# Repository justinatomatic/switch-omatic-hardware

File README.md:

## Switch-Omatic Board design

Eagle files for the Switch-Omatic project aka Wireless SmartHome Buttons. 

Current prototypes are using the 0.2 files
0.3 is work in progress for the next version. 

Parts from the Sparkfun and Adafruit libraries used.

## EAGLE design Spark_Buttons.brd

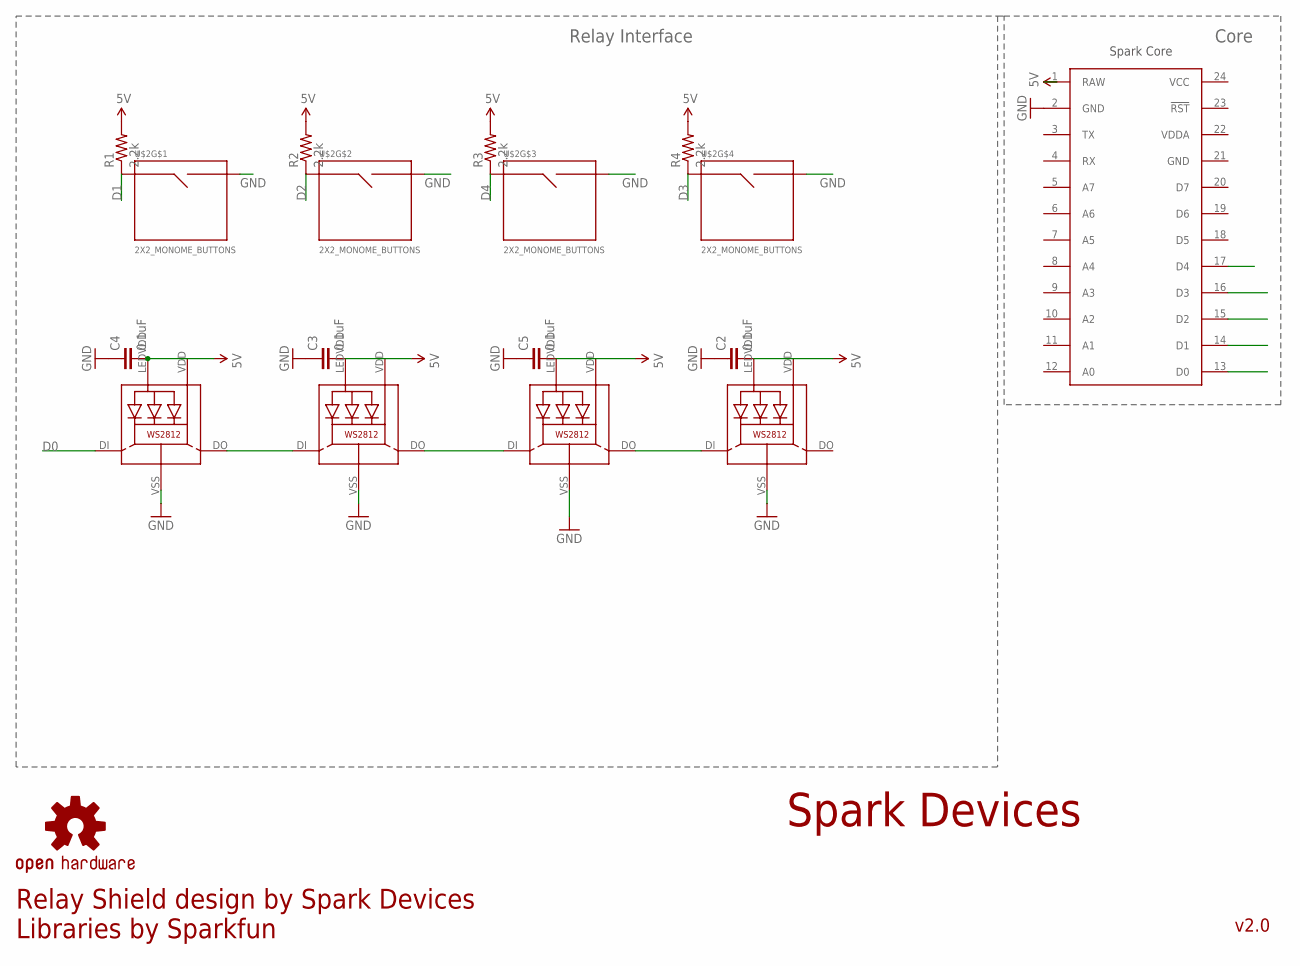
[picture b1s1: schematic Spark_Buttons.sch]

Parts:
C2, C3, C4, C5: 0.1uF; 0603-CAP
LED1, LED2, LED3, LED4: WS2812
LOGO1: OSHW-LOGOM; OSHW-LOGO-M
R1, R2, R3, R4: 2.2k; 0603-RES
U$1: SPARK_CORECORE; SPARK_CORE
U$2: 2X2_MONOME_BUTTONS; 2X2_MONOME_PAD

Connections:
5V: C2.2, C3.2, C4.2, C5.2, LED1.LEDVDD, LED1.VDD, LED2.LEDVDD, LED2.VDD, LED3.LEDVDD, LED3.VDD, LED4.LEDVDD, LED4.VDD, R1.2, R2.2, R3.2, R4.2, U$1.1 (RAW)
D0: LED1.DI, U$1.13 (D0)
D1: R1.1, U$1.14 (D1), U$2.SIG1
D2: R2.1, U$1.15 (D2), U$2.SIG3 (SIG1)
D3: R4.1, U$1.16 (D3), U$2.SIG7 (SIG1)
D4: R3.1, U$1.17 (D4), U$2.SIG5 (SIG1)
GND: C2.1, C3.1, C4.1, C5.1, LED1.VSS (GND), LED2.VSS (GND), LED3.VSS (GND), LED4.VSS (GND), U$1.2 (GND), U$1.21 (GND), U$2.SIG2, U$2.SIG4 (SIG2), U$2.SIG6 (SIG2), U$2.SIG8 (SIG2)
unnamed: LED1.DO, LED2.DI
unnamed: LED2.DO, LED3.DI
unnamed: LED3.DO, LED4.DI
VCC: U$1.24 (VCC)
VDDA: U$1.22 (VDDA)

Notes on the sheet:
Spark Core
Spark Devices
Core
Relay Interface
Relay Shield design by Spark Devices Libraries by Sparkfun
v2.0

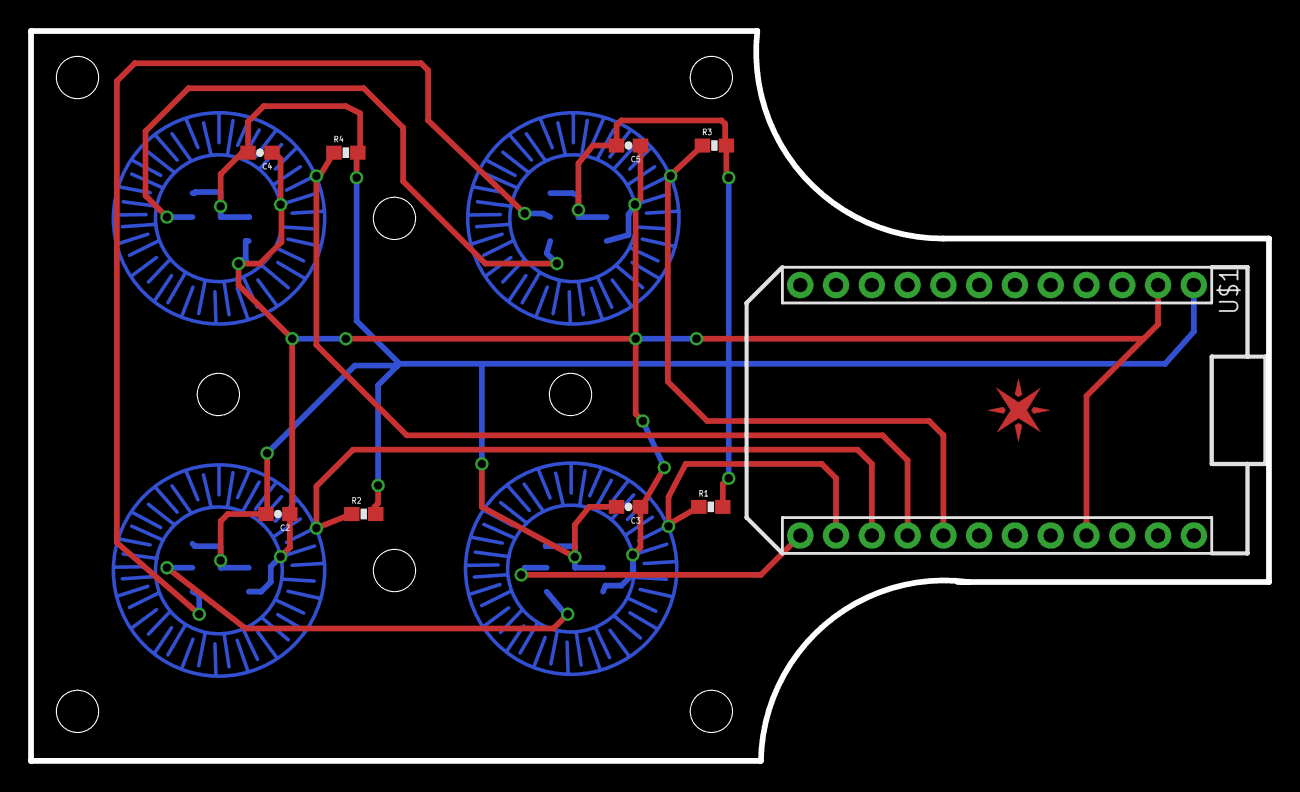
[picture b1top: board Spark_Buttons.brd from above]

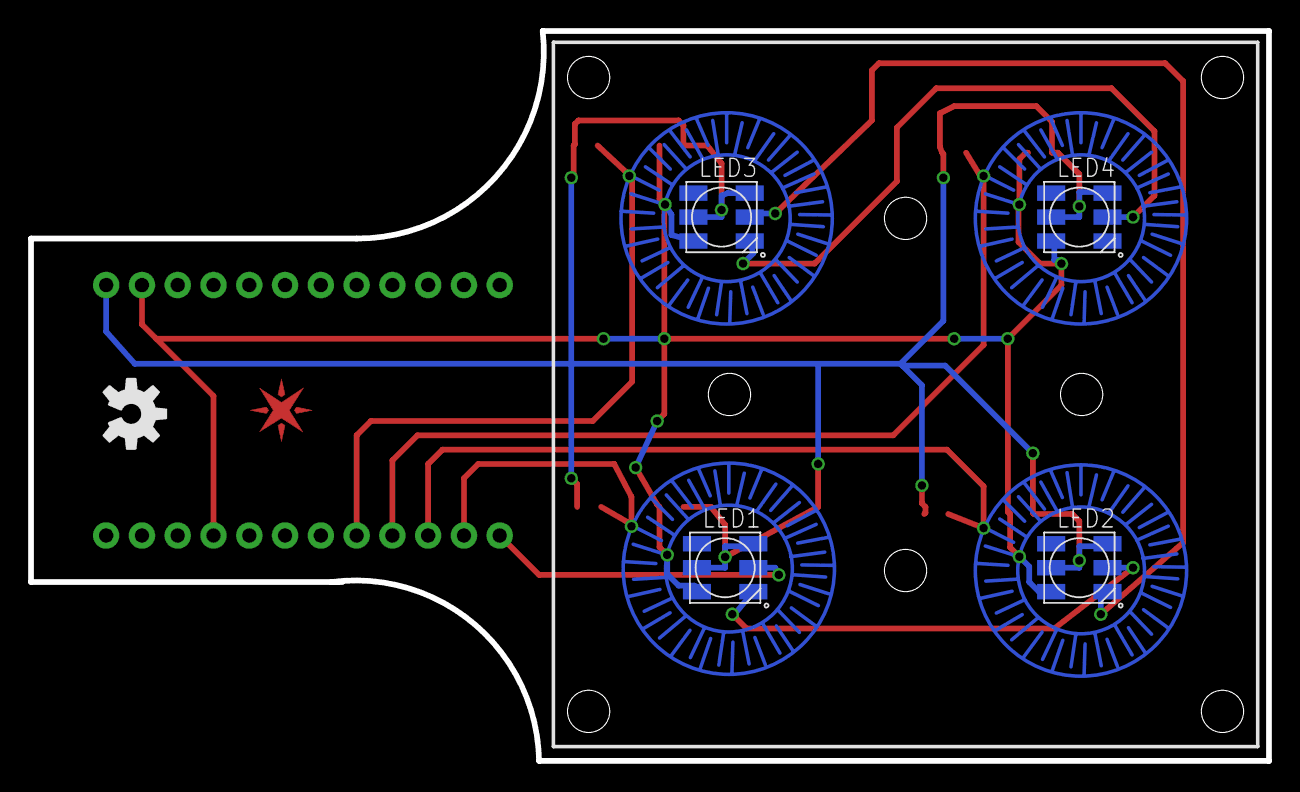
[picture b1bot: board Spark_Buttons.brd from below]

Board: 2 copper layers, 87.9 x 51.8 mm, 16 parts (6 on the bottom side), 10 nets.

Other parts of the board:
E$1: SPARK_LOGO_PLUS_PLANE

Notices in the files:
parts and their libraries:
SparkFun-Capacitors: Licensing: CC v3.0 Share-Alike You are welcome to use this library for commercial purposes.
